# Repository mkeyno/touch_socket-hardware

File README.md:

#  IoT Wall touch Socket 

This is a hardware of Wall touch Socket with three-channel output, one lighting sensor, and one temperature sensor
This IoT product can control any 

### lighting

### Home Appliance

### HVAC system

device in thr building (BMS)

# Final product

# Prototype

# schematic

# PCB
,,

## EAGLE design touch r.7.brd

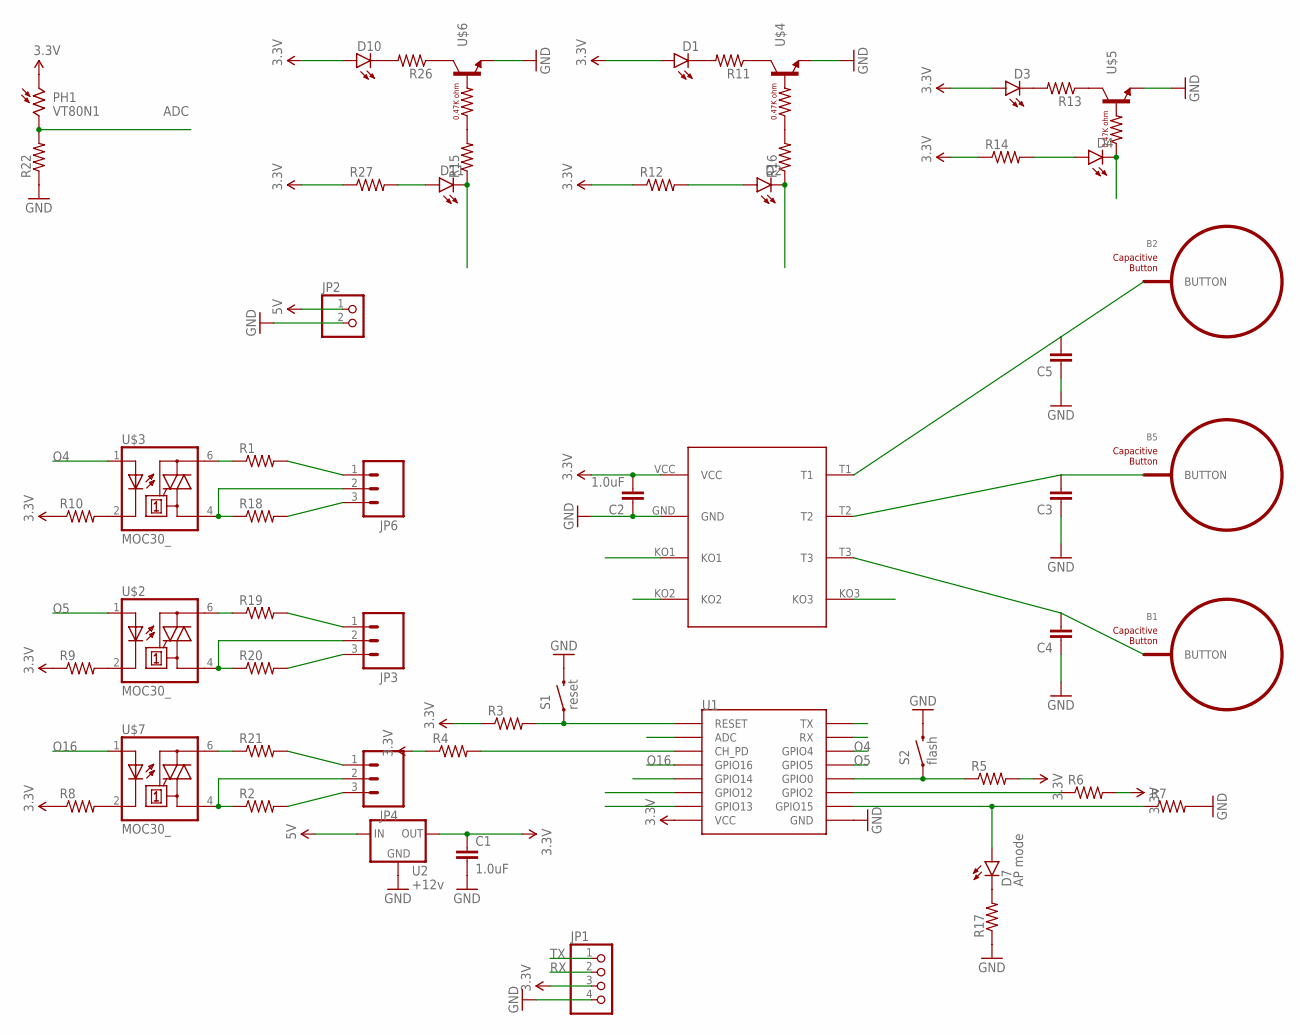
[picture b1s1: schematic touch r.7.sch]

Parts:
B1, B2, B5: BUTTON_PASSIVE12MM; BUTTON_PASSIVE_12MM
C1, C2: 1.0uF; 1206
C3, C4, C5: 1.0UF-25V-+80/-20(0805)"; 0805-CAP
D1, D2, D3, D4, D10, D11: LED-GREENLILYPAD; LED-1206
D7: AP mode; LED-1206
JP1: PINHD-1X4; 1X04
JP2: PINHD-1X2; 1X02
JP3, JP4, JP6: M03LONGPADS; 1X03_LONGPADS
PH1: VT80N1; VT800
R1, R2, R18, R19, R20, R21: RESISTORPTH-1/2W; AXIAL-0.5
R3, R4, R5, R6, R7, R8, R9, R10, R11, R12, R13, R14, R15, R16, R17, R22, R26, R27: 0.3OHM-1/8W-1%(0805); 0805
S1: reset; TACTILE-SWITCH-1101NE
S2: flash; TACTILE-SWITCH-1101NE
U1: ESP12SMD; ESP12-SMD
U2: +12v; TO-252
U$1: BS813A; BS813A_8PIN
U$2, U$3, U$7: MOC30_; MOC_
U$4, U$5, U$6: TRANSISTOR-NPN-DDTD142TC; SOT23-3

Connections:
3.3V: C1.1, C2.2, D1.A, D3.A, D10.A, JP1.3, PH1.1, R3.1, R4.1, R5.2, R6.2, R8.1, R9.1, R10.1, R12.1, R14.1, R27.1, U1.VCC, U2.2 (OUT), U$1.VCC
5V: JP2.1, U2.1 (IN)
12: U1.GPIO12, U$1.KO2
13: U1.GPIO13, U$1.KO1
14: U1.GPIO14, U$1.KO3
ADC: PH1.2, R22.2, U1.ADC
GND: C1.2, C2.1, C3.1, C4.1, C5.1, JP1.4, JP2.2, R7.2, R17.1, R22.1, S1.2, S2.2, U1.GND, U2.3 (GND), U$1.GND, U$4.2 (E), U$5.2 (E), U$6.2 (E)
unnamed: R1.P$1 (1), U$3.6
unnamed: JP6.2, R18.P$1 (1), U$3.4
unnamed: R19.P$1 (1), U$2.6
unnamed: JP3.2, R20.P$1 (1), U$2.4
unnamed: B5.BUTTON, C3.2, U$1.T2
unnamed: B1.BUTTON, C4.2, U$1.T3
unnamed: B2.BUTTON, C5.2, U$1.T1
unnamed: R3.2, S1.1, U1.RESET
unnamed: R4.2, U1.CH_PD
unnamed: R5.1, S2.1, U1.GPIO0
unnamed: R6.1, U1.GPIO2
unnamed: D7.A, R7.1, U1.GPIO15
unnamed: R8.2, U$7.2
unnamed: R9.2, U$2.2
unnamed: R10.2, U$3.2
unnamed: D2.A, R12.2
unnamed: D7.C, R17.2
unnamed: R15.2, U$6.1 (B)
unnamed: R11.1, U$4.3 (C)
unnamed: D1.C, R11.2
unnamed: D4.A, R14.2
unnamed: R16.2, U$4.1 (B)
unnamed: R21.P$1 (1), U$7.6
unnamed: JP4.2, R2.P$1 (1), U$7.4
unnamed: JP6.1, R1.P$2 (2)
unnamed: JP6.3, R18.P$2 (2)
unnamed: JP3.1, R19.P$2 (2)
unnamed: JP4.1, R21.P$2 (2)
unnamed: JP3.3, R20.P$2 (2)
unnamed: JP4.3, R2.P$2 (2)
unnamed: R13.1, U$5.3 (C)
unnamed: D3.C, R13.2
unnamed: D11.A, R27.2
unnamed: R26.1, U$6.3 (C)
unnamed: D10.C, R26.2
O4: D11.C, R15.1, U1.GPIO4, U$3.1
O5: D2.C, R16.1, U1.GPIO5, U$2.1
O16: D4.C, U1.GPIO16, U$5.1 (B), U$7.1
RX: JP1.2, U1.RXD0 (RX)
TX: JP1.1, U1.TXD0 (TX)

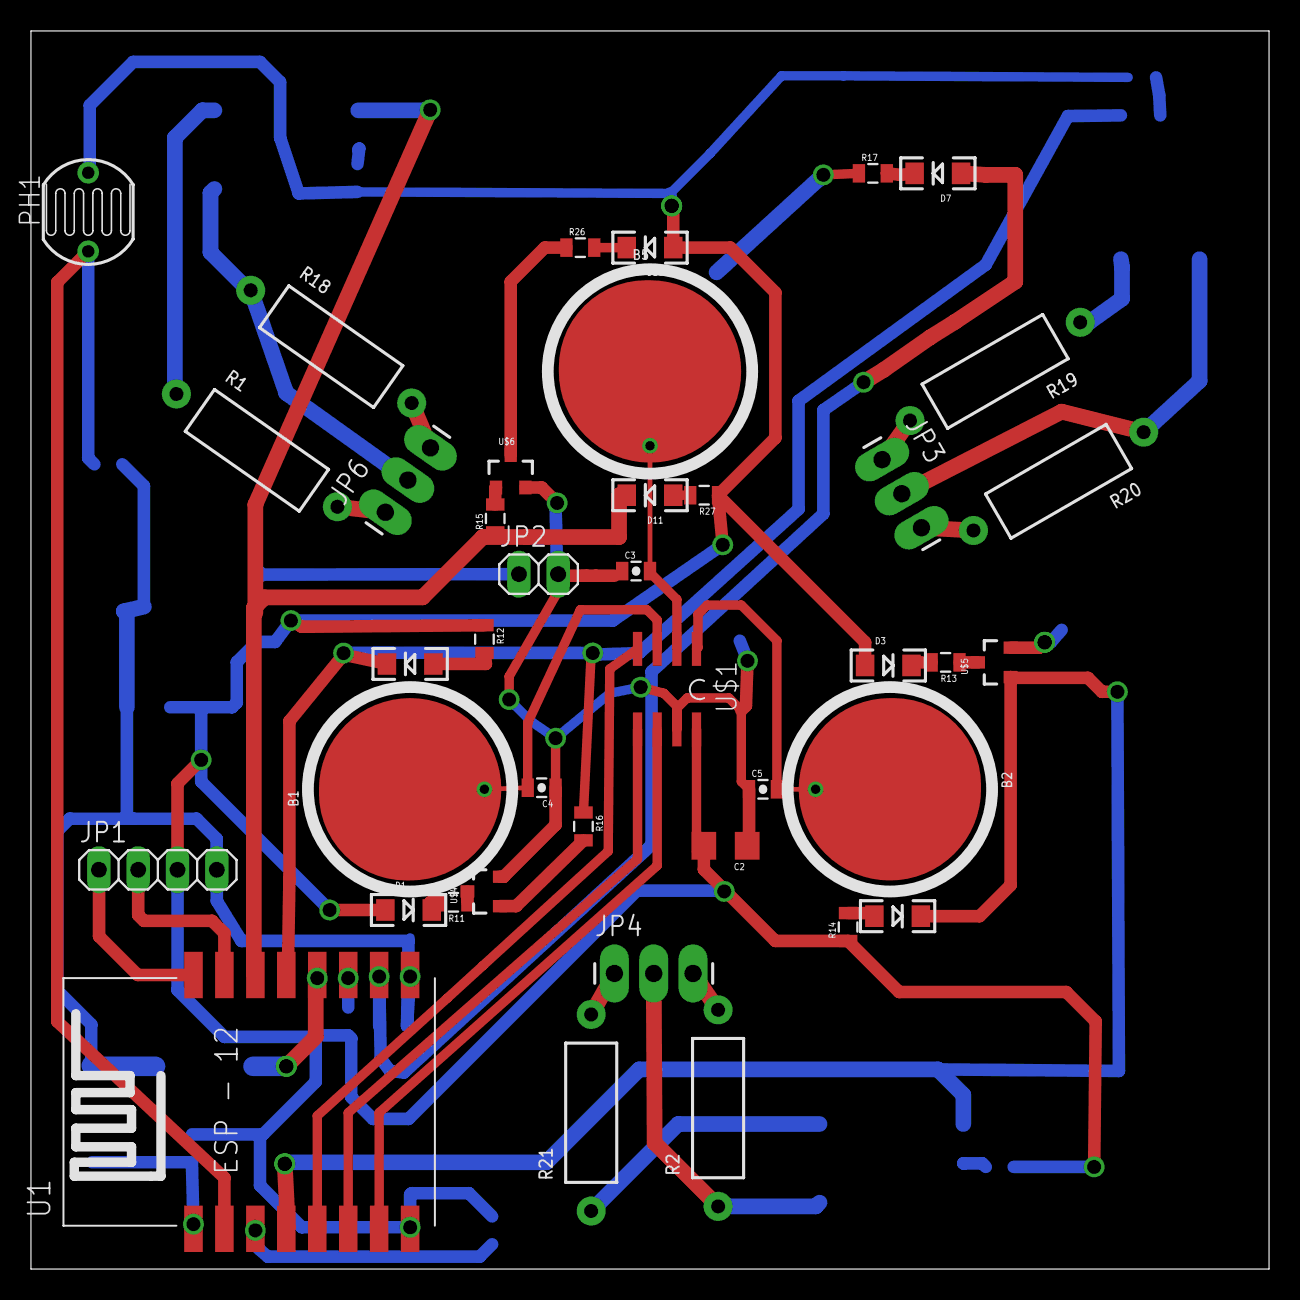
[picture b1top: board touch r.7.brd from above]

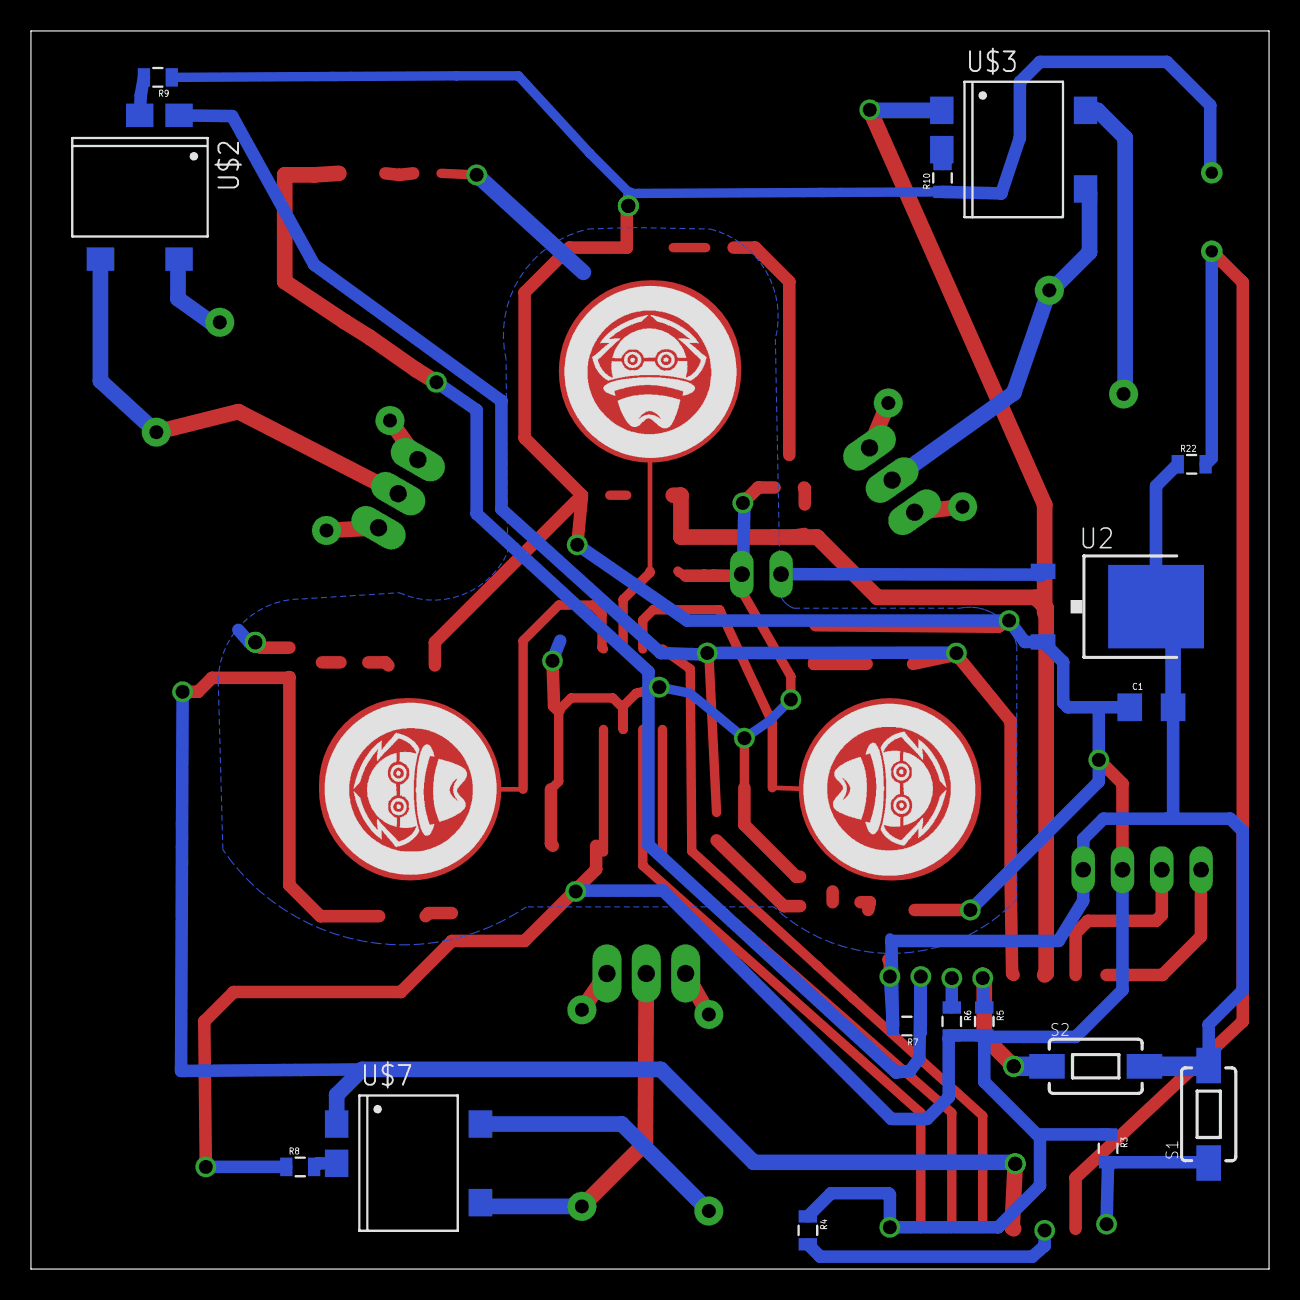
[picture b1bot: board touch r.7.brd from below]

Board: 2 copper layers, 80.0 x 80.0 mm, 56 parts (16 on the bottom side), 47 nets.

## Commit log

2020-11-30 new photos add

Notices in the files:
parts and their libraries:
PatternAgents-TouchWidgets: License : http://creativecommons.org/licenses/by-sa/4.0/ (Creative Commons 4.0)
PatternAgents-TouchWidgets: License : http://creativecommons.org/licenses/by-sa/3.1/ (Creative Commons 3.1)
